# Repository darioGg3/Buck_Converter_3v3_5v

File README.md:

# Buck Converter with 2 Outputs of 3v3 and 5v

PCB designed on KiCAD 6.0

### Specifications:
  - Two selectionable voltage outputs of 5V and 3,3V
  - Input voltage range: 6-28 VDC
  - Two SMD jumpers to select the desire output voltage.
  - Max output current: 500 mA.
  - Integrates the Texas Instrument IC [TPS54331](https://www.ti.com/lit/ds/symlink/tps54331.pdf) .
 <br>

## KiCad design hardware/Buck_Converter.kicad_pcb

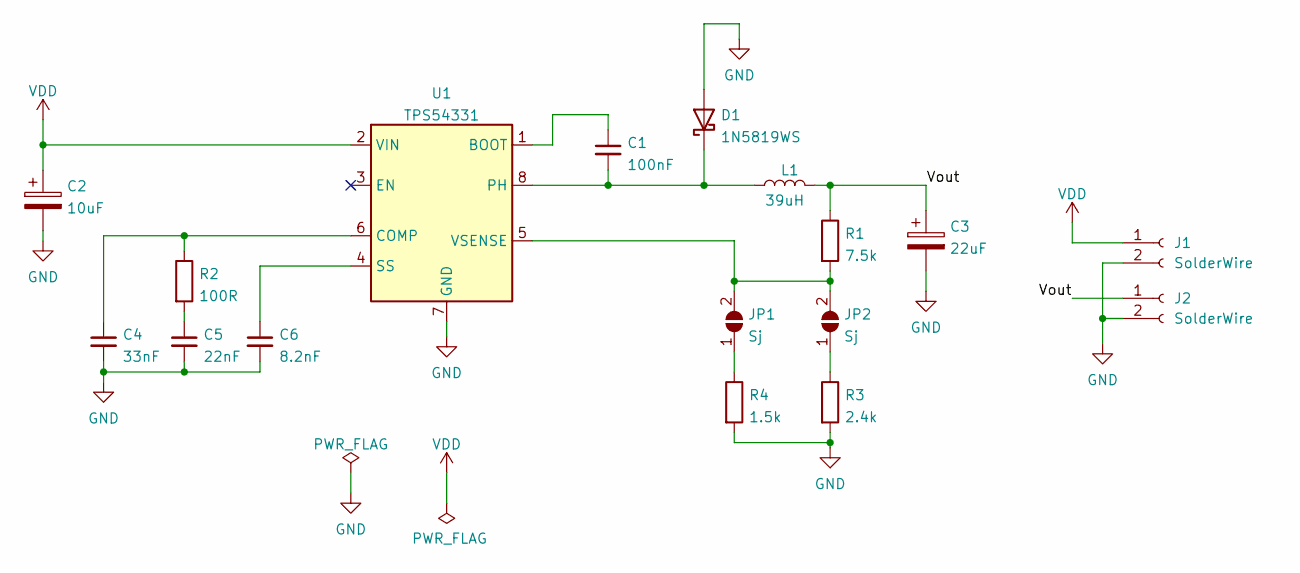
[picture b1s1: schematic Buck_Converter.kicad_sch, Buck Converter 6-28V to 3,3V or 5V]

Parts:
C1: 100nF; C_0402_1005Metric
C2: 10uF; CP_EIA-3216-10_Kemet-I
C3: 22uF; C_1206_3216Metric
C4: 33nF; C_0402_1005Metric
C5: 22nF; C_0402_1005Metric
C6: 8.2nF; C_0402_1005Metric
D1: 1N5819WS; D_SOD-323
J1, J2: SolderWire; SolderWire-0.5sqmm_1x02_P4.6mm_D0.9mm_OD2.1mm
JP1, JP2: Sj; SolderJumper-2_P1.3mm_Open_TrianglePad1.0x1.5mm
L1: 39uH; L_TracoPower_TCK-047_5.2x5.8mm
R1: 7.5k; R_0402_1005Metric
R2: 100R; R_0402_1005Metric
R3: 2.4k; R_0402_1005Metric
R4: 1.5k; R_0402_1005Metric
U1: TPS54331; SOIC-8_3.9x4.9mm_P1.27mm

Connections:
/Vout: C3.1, J2.1, L1.2, R1.1
GND: C2.2, C3.2, C4.2, C5.2, C6.2, D1.2 (A), J1.2, J2.2, R3.2, R4.2, U1.7 (GND)
unnamed: C1.1, U1.1 (BOOT)
unnamed: C1.2, D1.1 (K), L1.1, U1.8 (PH)
unnamed: C4.1, R2.1, U1.6 (COMP)
unnamed: C5.1, R2.2
unnamed: C6.1, U1.4 (SS)
unnamed: JP1.1 (A), R4.1
unnamed: JP1.2 (B), JP2.2 (B), R1.2, U1.5 (VSENSE)
unnamed: JP2.1 (A), R3.1
VDD: C2.1, J1.1, U1.2 (VIN)

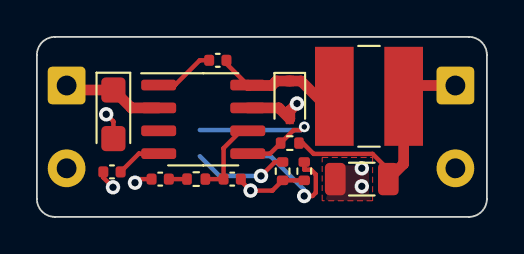
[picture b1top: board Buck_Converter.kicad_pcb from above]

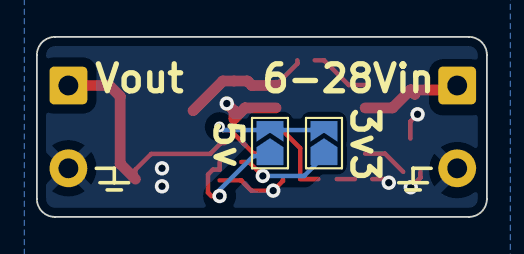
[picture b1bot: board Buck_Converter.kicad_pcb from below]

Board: 2 copper layers, 25.0 x 10.0 mm, 17 parts (2 on the bottom side), 11 nets.

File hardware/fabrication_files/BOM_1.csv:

"Id","Designator","Footprint","Quantity","Comment","Supplier and ref",
1,"J1,J2",SolderWire-0.5sqmm_1x02_P4.6mm_D0.9mm_OD2.1mm,2,SolderWire,
2,U1,SOIC-8_3.9x4.9mm_P1.27mm,1,TPS54331,
4,R1,R_0402_1005Metric,1,7.5k,
5,C3,C_1206_3216Metric,1,22uF,
6,C2,CP_EIA-3216-10_Kemet-I,1,10uF,
7,C5,C_0402_1005Metric,1,22nF,
8,C1,C_0402_1005Metric,1,100nF,
9,D1,D_SOD-323,1,1N5819WS,
10,R4,R_0402_1005Metric,1,1.5k,
11,C6,C_0402_1005Metric,1,8.2nF,
12,C4,C_0402_1005Metric,1,33nF,
13,R3,R_0402_1005Metric,1,2.4k,
14,R2,R_0402_1005Metric,1,100R,
15,"JP2,JP1",SolderJumper-2_P1.3mm_Open_TrianglePad1.0x1.5mm,2,Sj,

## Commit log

2022-04-15 schematic pdf modified
2022-05-25 update images
2025-03-20 version 9
